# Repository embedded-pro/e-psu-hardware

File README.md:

# e-psu — Hardware

e-psu is an open-source, USB-controlled front end for a 0–30 V / 10 A bench power supply. It sets the output voltage and current limit, measures current with auto-ranging down to µA resolution, and switches the output, similar to an Otii.

This repository holds the **KiCad** design (schematic and a fully routed 4-layer PCB), the scripts that generate and route the board, and the ngspice simulation of the analog stage. The board sits between an external 30 V bench supply and the load. An STM32G474 runs the control loops' setpoints, the range switching and the USB link.

> **Scope:** this repo is the *hardware*. Firmware is not part of it. The hardware facts the firmware must respect are listed in [Firmware constraints](#firmware-constraints).

| Top | Bottom |
|---|---|
|  |  |

> **Status: rev A, not built yet.** The schematic is complete and simulated. The board is fully routed: KiCad 7 DRC shows 0 errors and 0 unconnected items. See [Before ordering](#before-ordering).

---

## Highlights

- **Tracking pre-regulator plus linear stage.** An `LM76003` buck keeps VPRE about 1.5 V above the output. An `IRFP260N` source follower then gives a clean output with low dissipation.
- **Analog CV/CC loops.** `OPA2192` voltage and current error amps are diode-ORed onto the gate drive. Setpoints come from a `DAC80502`, and the loops were compensated from ngspice stability sweeps ([report](simulation/REPORT.md)).
- **Three current ranges, switched in hardware:**
  - 3 A on a 15 mΩ shunt with `INA293`;
  - 30 mA on 1 Ω with `INA190`;
  - 300 µA on 100 Ω with `INA190`.
  
  The bypass FETs sit on an isolated gate-drive island referenced to the output. Range-up is triggered by MCU comparators through timers, without firmware latency.
- **10 A pass-through path.** A 2 mΩ shunt with `INA281`, selected by a relay, measures current at the full 300 W.
- **Output switch.** Back-to-back `NTMFS5C430N` FETs driven by a `VOM1271` photovoltaic driver. The gate is held low at reset.
- **Hardware overcurrent clamp.** STM32G474 comparators drive the TIM20 break input, so the clamp acts within about 1 µs.
- **Isolated USB-C.** `ADuM3160` isolation, `USBLC6` ESD protection, and a separate ground plane for the PC side.
- **Input protection.** TVS, reverse-polarity P-FET, and fuses on both paths.

---

## Board architecture

The schematic is an 8-sheet hierarchical design. Each sheet is one functional block:

| Sheet | Function | Key parts |
|-------|----------|-----------|
| `e-psu.kicad_sch` | Top level: block overview, power flow, ground domains | — |
| `power_input` | 30 V input protection, housekeeping rails (+5 V, +3V3, +3.3VA, +5VA, VOP) | `SMBJ33CA`, `AOD4185`, `LMR16006X`, `AMS1117`, `TLV75533` |
| `buck` | Tracking pre-regulator (VPRE = VOUT + 1.5 V by DAC injection into FB) | `LM76003` |
| `linear` | Pass element, CV/CC loops, sense buffer, setpoint DAC, OCP clamp | `IRFP260N`, `OPA2192`, `OPA192`, `INA293`, `DAC80502` |
| `ranging` | Shunt ladder, range amplifiers, isolated gate-drive island | `INA190`, `AO3400A`, `B0505S`, `CA-IS3720HS`, `UCC27524A` |
| `output` | 10 A pass-through, mode relay, back-to-back output switch, terminals | `INA281`, `HF115F`, `NTMFS5C430N`, `VOM1271` |
| `mcu` | MCU pin map, SWD, LEDs, button, board NTC | `STM32G474RET6` |
| `usb` | Isolated USB-C | `USBLC6`, `ADuM3160` |

---

## Design requirements (spec)

These are the **hard design targets** the board must meet. They are the authoritative requirements for design review and sign-off.

| # | Requirement | Target |
|---|-------------|--------|
| R1 | Input | **30 V DC** from an external bench supply. Reverse-polarity and surge protected. |
| R2 | Output voltage | **0–30 V**, programmable (CV) |
| R3 | Output current, precision path | **3 A** max, programmable current limit (CC) |
| R4 | Output current, pass-through | **10 A** (300 W) through a relay-selected low-loss path |
| R5 | Current measurement | Auto-ranging **3 A / 30 mA / 300 µA**, µA resolution, hardware range-up |
| R6 | Output control | Output switch with a **safe state at reset** (output off, gate held low) |
| R7 | Protection | Hardware overcurrent clamp, fuses, input TVS, board temperature sensor |
| R8 | Host interface | **USB-C, galvanically isolated** from the power ground |
| R9 | PCB | **4 layers**, 100 × 100 mm, JLCPCB standard process and assembly |

### As-built component capability

| Parameter | Value |
|-----------|-------|
| Pre-regulator | `LM76003` synchronous buck, 500 kHz. VPRE = 33.8 V − 31.6 × BUCK_DAC. |
| Pass element | `IRFP260N` (TO-247) source follower at the board edge, ready for a heatsink |
| Control | Analog CV/CC loops (`OPA2192`), `DAC80502` setpoints, `OPA192` sense buffer |
| Current sense | 15 mΩ + `INA293` (3 A), 1 Ω / 100 Ω + `INA190` (30 mA / 300 µA), 2 mΩ + `INA281` (10 A) |
| Range switching | `AO3400A` bypass FETs, `BAV199` clamps, isolated island (`B0505S` + `CA-IS3720HS` + `UCC27524A`) |
| Output | `HF115F` mode relay; back-to-back `NTMFS5C430N` switch with a `VOM1271` driver |
| MCU | `STM32G474RET6`: comparators and timers for OCP and range-up, SWD |
| USB | USB-C, `USBLC6-2` ESD, `ADuM3160` full-speed isolator |
| PCB | 4 layers (F sig / In1 GND / In2 power / B sig), 1.6 mm, 1 oz outer + **1 oz inner**, 244 parts |

### Simulation results

The loops were checked across corners with ngspice. The compensation changes from the sweep are in schematic rev A1:

- CV loop phase margin: worst case 35°, median 63°.
- CC loop phase margin: at least 91°.
- A dead short peaks at 33 A for 0.9 µs with the hardware OCP armed.

Details are in [`simulation/REPORT.md`](simulation/REPORT.md).

### Firmware constraints

- Clamp **BUCK_DAC ≥ 0.2 V** (VPRE = 27.5 V). At 0 V, VPRE is commanded above VIN and the buck runs at maximum duty. In reset, the DAC pin is high-impedance, which gives a safe 2 V.
- Keep the **hardware OCP armed**: COMP3/4/6 → TIM20 BRK. Without it, a short is limited only by the analog CC loop, giving tens of amps for about 95 µs.
- **Range-up is in hardware:** COMP1 → TIM1 → RANGE_B and COMP2 → TIM8 → RANGE_A. Firmware only handles range-down.
- The analog CC loop cannot limit below about 30 mA. Lower limits need firmware supervision.

---

## Repository layout

```
e-psu-hardware/
├── hardware/                       # KiCad projects — one folder per board
│   └── e-psu/                      #   main board (KiCad 7 format)
│       ├── e-psu.kicad_pro
│       ├── e-psu.kicad_sch         #     top-level (root) schematic
│       ├── power_input / buck / linear / ranging / output / mcu / usb .kicad_sch
│       ├── e-psu.kicad_pcb         #     PCB layout (4 layers)
│       ├── e-psu.kicad_sym         #     project symbols
│       ├── e-psu.pretty/           #     project footprints
│       └── sym-lib-table, fp-lib-table
├── scripts/
│   ├── export_review.py            # review package     -> review_exports/<board>/
│   ├── export_jlcpcb.py            # fab + assembly     -> manufacturing/<board>/
│   ├── export_release.py           # release bundle     -> release/<board>-<version>.zip
│   ├── visual_diff.py              # PR visual diff     -> diff/<board>/
│   ├── pcb/                        # board generator: placement, power copper, router, renders
│   └── schgen/                     # schematic generator (one-way: overwrites hardware/e-psu/)
├── simulation/                     # ngspice suite of the analog stage + REPORT.md
├── docs/
│   ├── psu-hardware-design-guide.md   # design & review knowledge base
│   └── images/                     # board renders
├── .claude/agents/psu-board-reviewer.md   # design-review agent
├── PROJECT_CONTEXT.md              # design summary, decisions, open items
└── .github/workflows/              # CI: kicad-bot, kicad-diff, pcb-quality, release
```

> Each board is a self-contained KiCad project in its own `hardware/<board>/` folder. The `.kicad_pro`, root schematic and board share that folder. Generated outputs are gitignored and go to `review_exports/<board>/`, `manufacturing/<board>/` and `release/`.

---

## Getting started

This is a [**KiCad**](https://www.kicad.org/) project saved in KiCad 7 format. It opens in KiCad 7 or newer.

1. Clone the repository:
   ```bash
   git clone https://github.com/embedded-pro/e-psu-hardware.git
   cd e-psu-hardware
   ```
2. Open `hardware/e-psu/e-psu.kicad_pro` in KiCad.
3. Use the schematic editor for the hierarchical sheets, or the PCB editor for the layout.

### Headless checks (the same ones CI runs)

With KiCad 8 or newer installed, you can run the electrical and design-rule checks locally:

```bash
kicad-cli sch erc  --output erc.json --format json hardware/e-psu/e-psu.kicad_sch
kicad-cli pcb drc  --output drc.json --format json --schematic-parity hardware/e-psu/e-psu.kicad_pcb
```

The export helpers produce the full packages:
- `python scripts/export_review.py` builds the review package;
- `python scripts/export_jlcpcb.py` builds the JLCPCB fab and assembly files.

### Regenerating the board and the simulation

- `scripts/pcb/make_board.py --own` rebuilds and re-routes the board from the schematic. It needs KiCad 7 and pcbnew; see [`scripts/pcb/README.md`](scripts/pcb/README.md).
- `simulation/sweep.py` and `simulation/make_plots.py` rerun the analog simulation with ngspice; see [`simulation/README.md`](simulation/README.md).

---

## Before ordering

1. **Replace the U201 footprint.** The `LM76003` land (TI RNP0030B, WQFN-30, 6 × 4 mm) in `e-psu.pretty` is provisional.
   - Get the real one from TI, or from LCSC/EasyEDA (C470958).
   - Save it as `e-psu:TI_RNP0030B_WQFN-30`.
   - Re-route the buck corner, either with `scripts/pcb/make_board.py --own` or by hand.
2. **Check these pinouts against the makers' drawings:**
   - K501 `HF115F`, mapped onto the KiCad Schrack RT1 footprint;
   - PS401 `B0505S`;
   - U502 `VOM1271`: pin 4 is assumed to be +.
3. **Get ERC clean.** kicad-bot runs it on every push.
4. **JLCPCB order options:**
   - 4 layers, 1.6 mm, **1 oz inner copper** (needed for the 10 A path on In2);
   - "Specify a location" for the order number (the `JLCJLCJLCJLC` text on the bottom);
   - check every rotation in the CPL preview.
5. **Add LCSC part numbers** for the passives that don't have one yet. THT parts are hand-soldered or ordered as THT assembly: banana jacks, F102, K501, Q301, PS401.

---

## Continuous integration

Every push and pull request is checked by [**kicad-bot**](https://github.com/embedded-pro/kicad-bot). It is a CI quality gate that wraps `kicad-cli`, KiBot, KiCost and KiDiff, and runs:

- **ERC / DRC verification:** electrical and design-rule checks, with schematic parity.
- **BOM availability:** distributor stock and lifecycle flags (not available in kicad-bot yet).
- **Visual diffs:** for pull requests, [`kicad-diff.yml`](.github/workflows/kicad-diff.yml) renders the base and head with `kicad-cli` and uploads red/green overlays.
- **Layout quality:** for pull requests, [`pcb-quality.yml`](.github/workflows/pcb-quality.yml) runs a hard short/clearance gate (exclusions ignored, plus the fab minimum), DRC and geometry gates (45° corners only, no mid-track branches, jogs, segments and vias per connection) with `pcb_rules.py` from the [`pcb-design-rules`](https://github.com/gabrielfrasantos/claude-hardware-skills/tree/main/plugins/hardware-design/skills/pcb-design-rules) skill. The report is in the job summary. It stays red until the board is re-laid out.

The workflow is [`.github/workflows/kicad-bot.yml`](.github/workflows/kicad-bot.yml). It uploads a `kicad-bot-output-<board>` artifact containing the report, metrics and raw violation data.

> kicad-bot is a CI guardrail, **not** a substitute for design review or sign-off. For a review, use the `psu-board-reviewer` agent in [`.claude/agents/`](.claude/agents/).

All third-party actions are **pinned to a full commit SHA**, with the version in a trailing comment, for supply-chain hardening.

## Releases

Releases are automated with [release-please](https://github.com/googleapis/release-please) and driven by [Conventional Commits](https://www.conventionalcommits.org/) (`feat:`, `fix:`, …). The flow, defined in [`.github/workflows/release.yml`](.github/workflows/release.yml):

1. Commits to `main` keep an open **release PR** with the next version bump and the `CHANGELOG.md` entries.
2. Merging that PR cuts a **GitHub Release** and a tag. The first release is `v0.1.0`.
3. On release, kicad-bot re-runs **ERC/DRC**, so a release requires a clean design. Then `scripts/export_release.py` builds `e-psu-<version>.zip` and attaches it to the release. The zip contains:
   - the schematic PDF;
   - board PDFs (copper and silkscreen, inner layers included);
   - Gerbers and drill files;
   - BOM and CPL.

Version state is tracked in [`.release-please-manifest.json`](.release-please-manifest.json). The behaviour is configured in [`release-please-config.json`](release-please-config.json).

---

## License

Released under the [CERN Open Hardware Licence Version 2 – Permissive](LICENSE) (CERN-OHL-P-2.0).

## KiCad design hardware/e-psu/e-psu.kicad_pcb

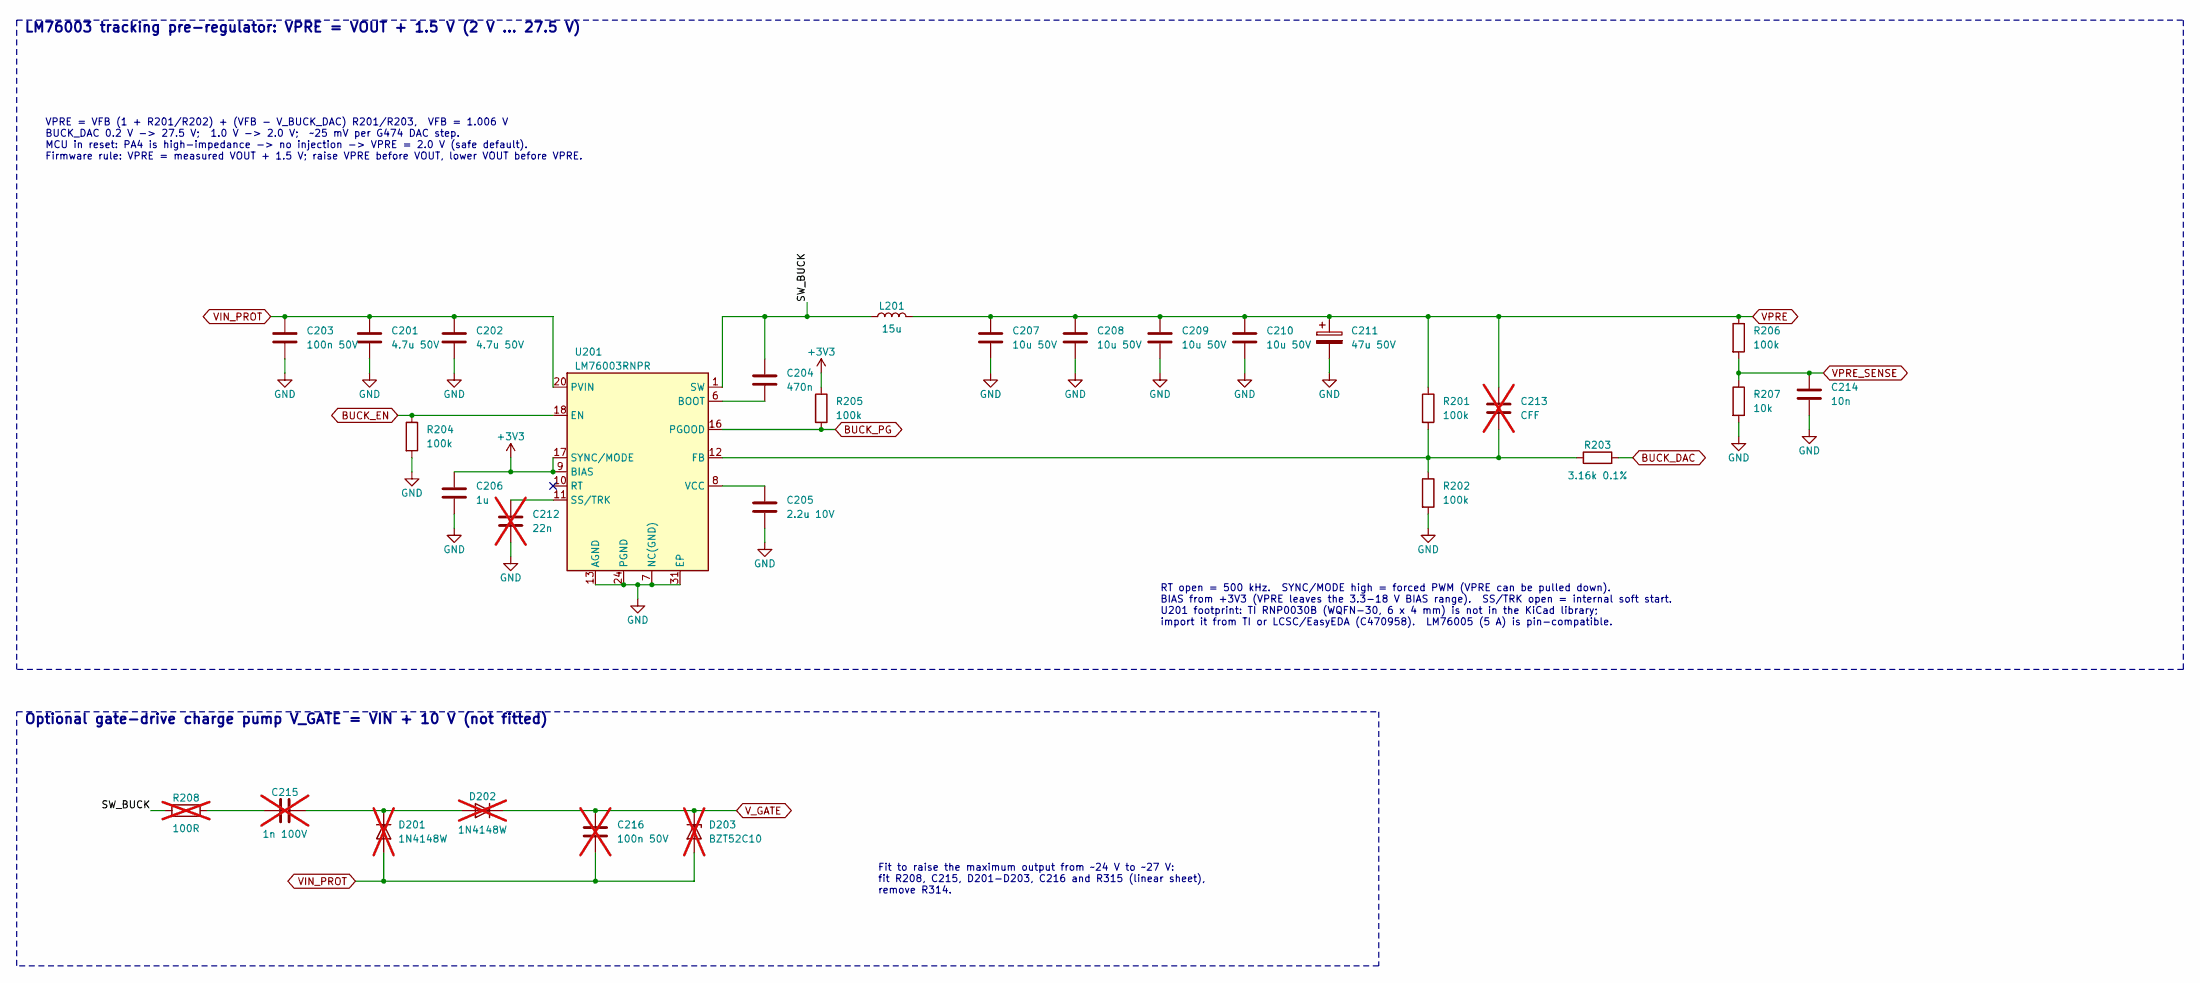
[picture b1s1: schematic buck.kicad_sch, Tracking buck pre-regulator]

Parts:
C201, C202: 4.7u 50V; C_1210_3225Metric
C203: 100n 50V; C_0603_1608Metric
C204: 470n; C_0603_1608Metric
C205: 2.2u 10V; C_0603_1608Metric
C206: 1u; C_0603_1608Metric
C207, C208, C209, C210: 10u 50V; C_1210_3225Metric
C211: 47u 50V; CP_Elec_8x10
C212: 22n; C_0603_1608Metric; not fitted
C213: CFF; C_0603_1608Metric; not fitted
C214: 10n; C_0603_1608Metric
C215: 1n 100V; C_0603_1608Metric; not fitted
C216: 100n 50V; C_0603_1608Metric; not fitted
D201, D202: 1N4148W; D_SOD-123; not fitted
D203: BZT52C10; D_SOD-123; not fitted
L201: 15u; L_Wuerth_HCI-1350; MPN FANGCHENG FCH1365-150M (Isat 12 A); LCSC C20415554
R201, R202, R204, R205, R206: 100k; R_0603_1608Metric
R203: 3.16k 0.1%; R_0603_1608Metric
R207: 10k; R_0603_1608Metric
R208: 100R; R_0603_1608Metric; not fitted
U201: LM76003RNPR; TI_RNP0030B_WQFN-30; MPN TI LM76003RNPR; LCSC C470958

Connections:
+3V3: C206.1, R205.1, U201.9 (BIAS), U201.17 (SYNC/MODE); also elsewhere on the board
/Tracking buck pre-regulator/SW_BUCK: C204.1, L201.1, R208.1, U201.1 (SW), U201.2 (SW), U201.3 (SW), U201.4 (SW), U201.5 (SW)
BUCK_DAC: R203.2; also elsewhere on the board
BUCK_EN: R204.1, U201.18 (EN); also elsewhere on the board
BUCK_PG: R205.2, U201.16 (PGOOD); also elsewhere on the board
GND: C201.2, C202.2, C203.2, C205.2, C206.2, C207.2, C208.2, C209.2, C210.2, C211.2, C212.2, C214.2, R202.2, R204.2, R207.2, U201.7 (NC(GND)), U201.13 (AGND), U201.14 (AGND), U201.15 (AGND), U201.19 (NC(GND)), U201.23 (NC(GND)), U201.24 (PGND), U201.25 (PGND), U201.26 (PGND), U201.27 (NC(GND)), U201.28 (NC(GND)), U201.29 (NC(GND)), U201.30 (NC(GND)), U201.31 (EP); also elsewhere on the board
unnamed: C215.1, R208.2
unnamed: C215.2, D201.1 (K), D202.2 (A)
unnamed: C204.2, U201.6 (BOOT)
unnamed: C213.2, R201.2, R202.1, R203.1, U201.12 (FB)
unnamed: C212.1, U201.11 (SS/TRK)
unnamed: C205.1, U201.8 (VCC)
VIN_PROT: C201.1, C202.1, C203.1, C216.2, D201.2 (A), D203.2 (A), U201.20 (PVIN), U201.21 (PVIN), U201.22 (PVIN); also elsewhere on the board
VPRE: C207.1, C208.1, C209.1, C210.1, C211.1, C213.1, L201.2, R201.1, R206.1; also elsewhere on the board
VPRE_SENSE: C214.1, R206.2, R207.1; also elsewhere on the board
V_GATE: C216.1, D202.1 (K), D203.1 (K); also elsewhere on the board

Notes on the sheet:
LM76003 tracking pre-regulator: VPRE = VOUT + 1.5 V (2 V ... 27.5 V)
VPRE = VFB (1 + R201/R202) + (VFB - V_BUCK_DAC) R201/R203, VFB = 1.006 V BUCK_DAC 0.2 V -> 27.5 V; 1.0 V -> 2.0 V; ~25 mV per G474 DAC step. MCU in reset: PA4 is high-impedance -> no injection -> VPRE = 2.0 V (safe default). Firmware rule: VPRE = measured VOUT + 1.5 V; raise VPRE before VOUT, lower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
RT open = 500 kHz. SYNC/MODE high = forced PWM (VPRE can be pulled down). BIAS from +3V3 (VPRE leaves the 3.3-18 V BIAS range). SS/TRK open = internal soft start. U201 footprint: TI RNP0030B (WQFN-30, 6 x 4 mm) is not in the KiCad library; import it from TI or LCSC/EasyEDA (C470958). LM76005 (5 A) 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
Optional gate-drive charge pump V_GATE = VIN + 10 V (not fitted)
Fit to raise the maximum output from ~24 V to ~27 V: fit R208, C215, D201-D203, C216 and R315 (linear sheet), remove R314.

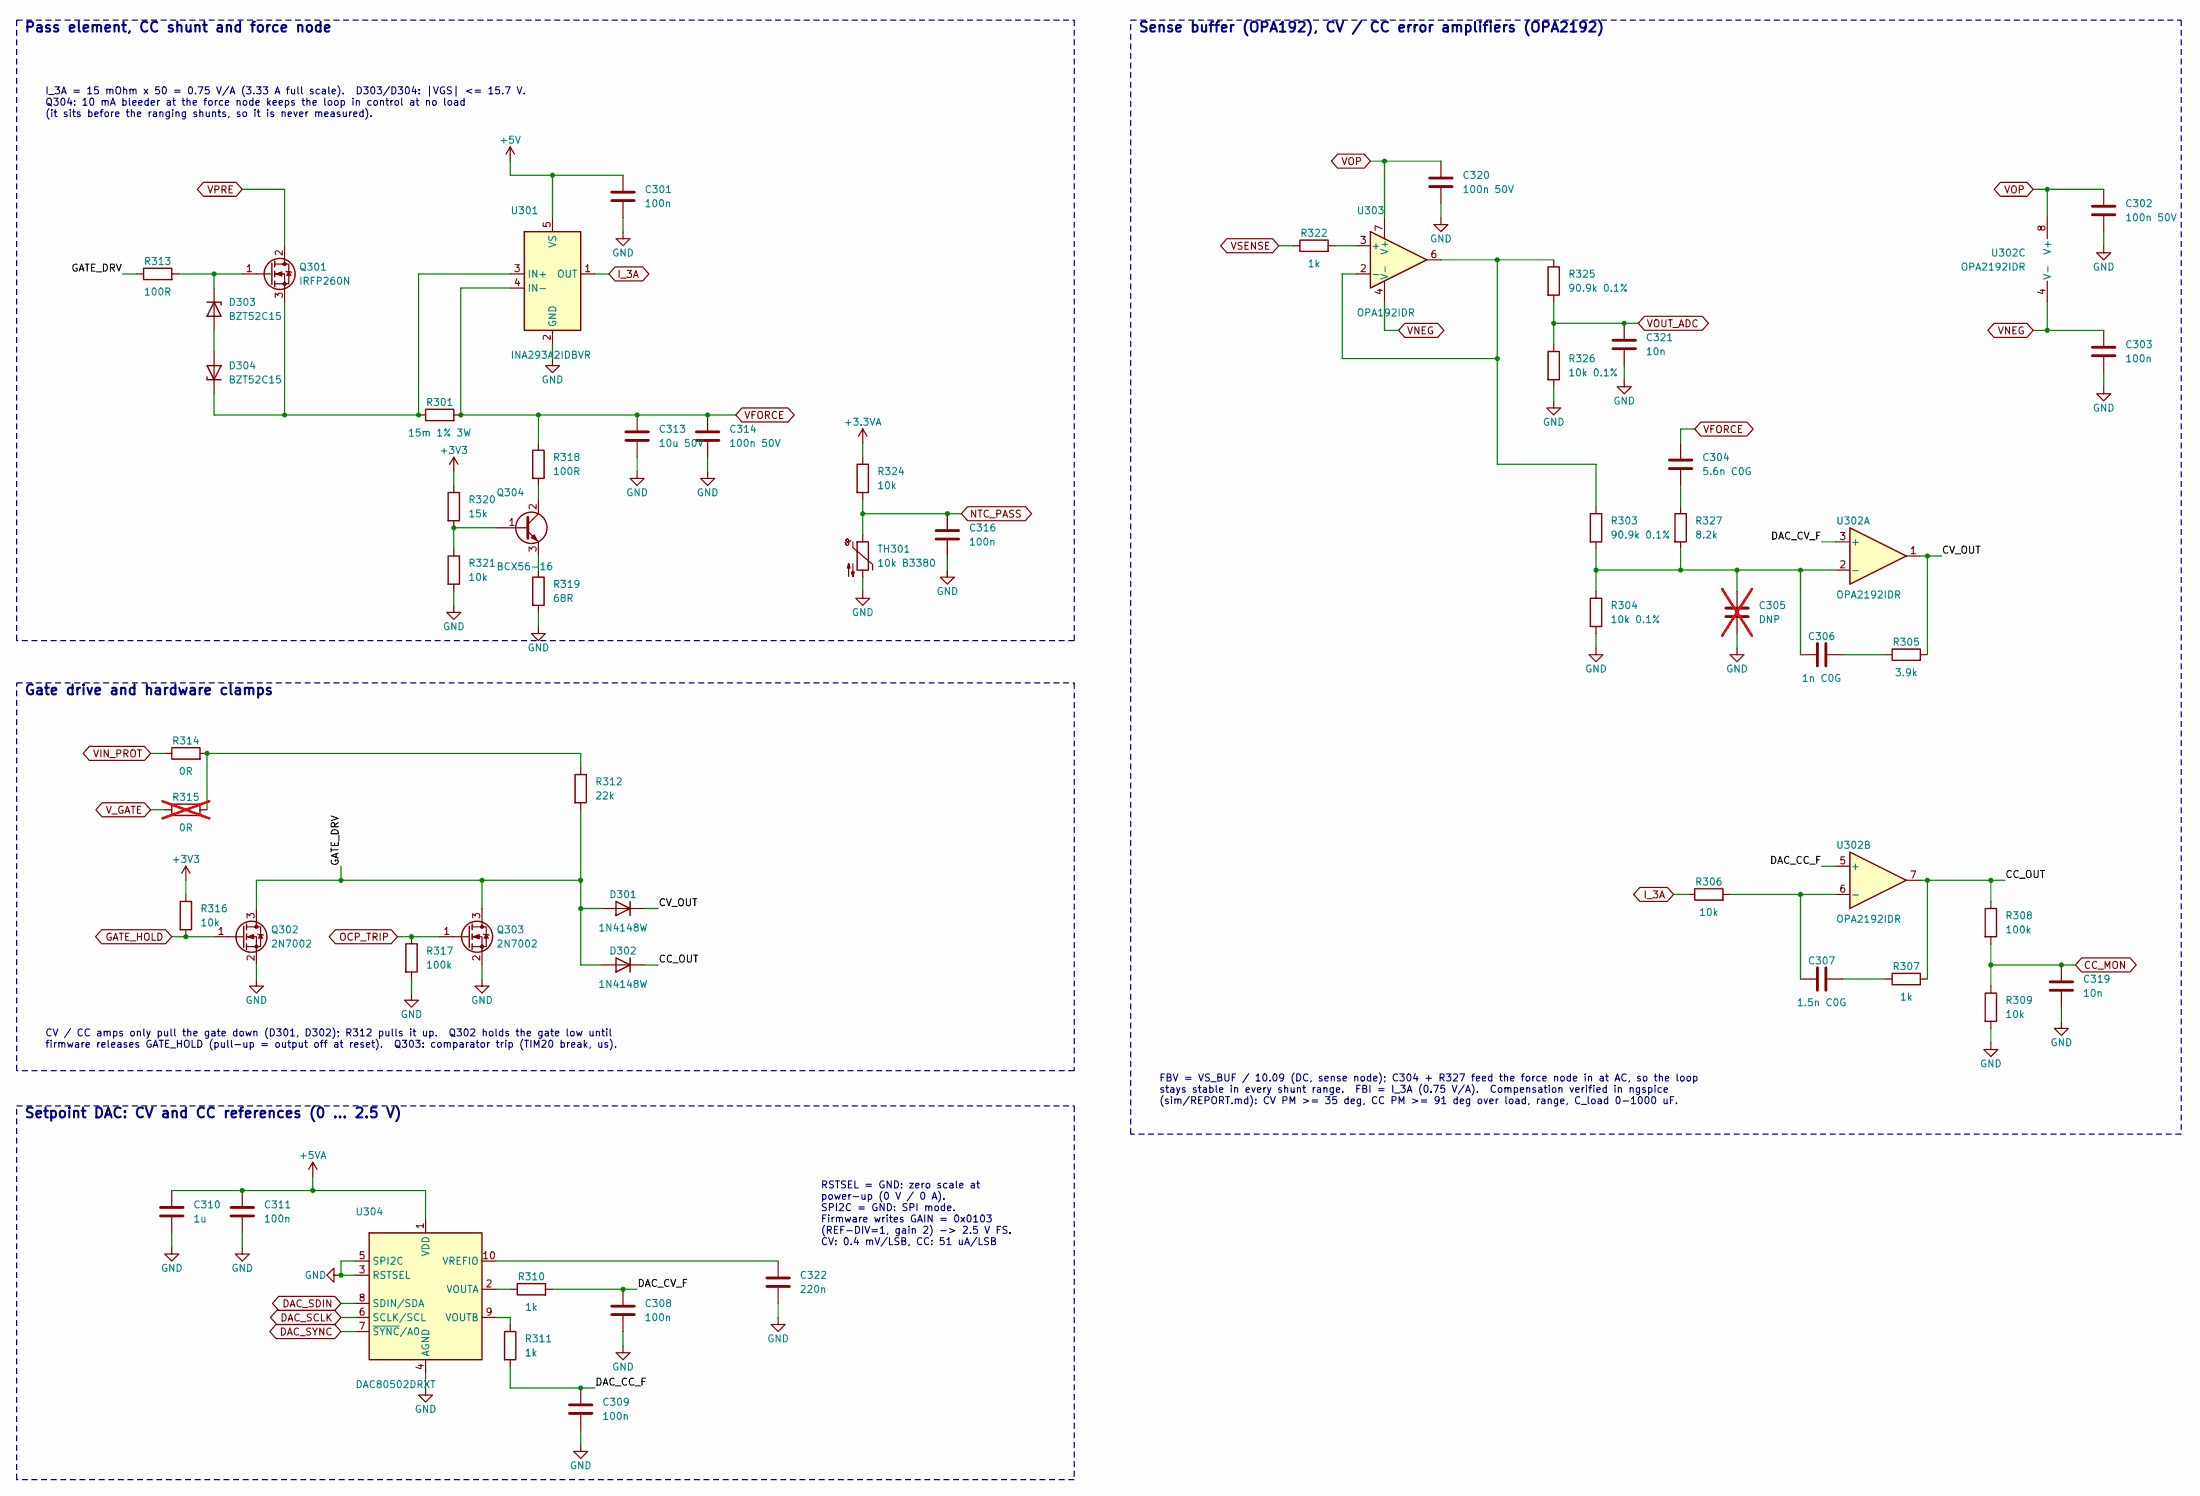
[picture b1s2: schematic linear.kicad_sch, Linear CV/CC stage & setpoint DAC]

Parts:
C301, C303, C308, C309, C311, C316: 100n; C_0603_1608Metric
C302, C314, C320: 100n 50V; C_0603_1608Metric
C304: 5.6n C0G; C_0603_1608Metric
C305: DNP; C_0603_1608Metric; not fitted
C306: 1n C0G; C_0603_1608Metric
C307: 1.5n C0G; C_0603_1608Metric
C310: 1u; C_0603_1608Metric
C313: 10u 50V; C_1210_3225Metric
C319, C321: 10n; C_0603_1608Metric
C322: 220n; C_0603_1608Metric
D301, D302: 1N4148W; D_SOD-123
D303, D304: BZT52C15; D_SOD-123
Q301: IRFP260N; TO-247-3_Vertical; MPN Infineon IRFP260NPBF on heatsink (or a 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; LCSC C2678
Q302, Q303: 2N7002; SOT-23
Q304: BCX56-16; SOT-89-3; MPN BCX56-16 (SOT-89, 1 W): ~0.25 W at 24 V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
R301: 15m 1% 3W; R_2512_6332Metric; LCSC C459682
R303, R325: 90.9k 0.1%; R_0603_1608Metric
R304, R326: 10k 0.1%; R_0603_1608Metric
R305: 3.9k; R_0603_1608Metric
R306, R309, R316, R321, R324: 10k; R_0603_1608Metric
R307, R310, R311, R322: 1k; R_0603_1608Metric
R308, R317: 100k; R_0603_1608Metric
R312: 22k; R_0603_1608Metric
R313, R318: 100R; R_0603_1608Metric
R314: 0R; R_0603_1608Metric
R315: 0R; R_0603_1608Metric; not fitted
R319: 68R; R_0805_2012Metric
R320: 15k; R_0603_1608Metric
R327: 8.2k; R_0603_1608Metric
TH301: 10k B3380; R_0603_1608Metric; MPN Murata NCP18XH103F03RB, on the heatsink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; LCSC C13564
U301: INA293A2IDBVR; SOT-23-5; LCSC C1855792
U302: OPA2192IDR; SOIC-8_3.9x4.9mm_P1.27mm; LCSC C110074
U303: OPA192IDR; SOIC-8_3.9x4.9mm_P1.27mm; LCSC C2861286
U304: DAC80502DRXT; Texas_DRX_WSON-10_2.5x2.5mm_P0.5mm; LCSC C2861168

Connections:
+3.3VA: R324.1; also elsewhere on the board
+3V3: R316.1, R320.1; also elsewhere on the board
+5V: C301.1, U301.5 (VS); also elsewhere on the board
+5VA: C310.1, C311.1, U304.1 (VDD); also elsewhere on the board
/Linear CV/CC stage & setpoint DAC/CC_OUT: D302.1 (K), R307.2, R308.1, U302.7
/Linear CV/CC stage & setpoint DAC/CV_OUT: D301.1 (K), R305.2, U302.1
/Linear CV/CC stage & setpoint DAC/DAC_CC_F: C309.1, R311.2, U302.5 (+)
/Linear CV/CC stage & setpoint DAC/DAC_CV_F: C308.1, R310.2, U302.3 (+)
/Linear CV/CC stage & setpoint DAC/GATE_DRV: D301.2 (A), D302.2 (A), Q302.3 (D), Q303.3 (D), R312.2, R313.1
CC_MON: C319.1, R308.2, R309.1; also elsewhere on the board
DAC_SCLK: U304.6 (SCLK/SCL); also elsewhere on the board
DAC_SDIN: U304.8 (SDIN/SDA); also elsewhere on the board
DAC_SYNC: U304.7 (~SYNC/A0); also elsewhere on the board
GATE_HOLD: Q302.1 (G), R316.2; also elsewhere on the board
GND: C301.2, C302.2, C303.2, C305.2, C308.2, C309.2, C310.2, C311.2, C313.2, C314.2, C316.2, C319.2, C320.2, C321.2, C322.2, Q302.2 (S), Q303.2 (S), R304.2, R309.2, R317.2, R319.2, R321.2, R326.2, TH301.2, U301.2 (GND), U304.3 (RSTSEL), U304.4 (AGND), U304.5 (SPI2C); also elsewhere on the board
I_3A: R306.1, U301.1 (OUT); also elsewhere on the board
NTC_PASS: C316.1, R324.2, TH301.1; also elsewhere on the board
unnamed: C304.2, R327.1
unnamed: C306.2, R305.1
unnamed: C307.2, R307.1
unnamed: D303.2 (A), D304.2 (A)
unnamed: D303.1 (K), Q301.1 (G), R313.2
unnamed: D304.1 (K), Q301.3 (S), R301.1, U301.3 (IN+)
unnamed: Q304.1 (B), R320.2, R321.1
unnamed: Q304.2 (C), R318.2
unnamed: Q304.3 (E), R319.1
unnamed: R312.1, R314.2, R315.2
unnamed: C305.1, C306.1, R303.2, R304.1, R327.2, U302.2 (-)
unnamed: C307.1, R306.2, U302.6 (-)
unnamed: R322.2, U303.3 (+)
unnamed: R303.1, R325.1, U303.2 (-), U303.6
unnamed: R310.1, U304.2 (VOUTA)
unnamed: R311.1, U304.9 (VOUTB)
unnamed: C322.1, U304.10 (VREFIO)
OCP_TRIP: Q303.1 (G), R317.1; also elsewhere on the board
VFORCE: C304.1, C313.1, C314.1, R301.2, R318.1, U301.4 (IN-); also elsewhere on the board
VIN_PROT: R314.1; also elsewhere on the board
VNEG: C303.1, U302.4 (V-), U303.4 (V-); also elsewhere on the board
VOP: C302.1, C320.1, U302.8 (V+), U303.7 (V+); also elsewhere on the board
VOUT_ADC: C321.1, R325.2, R326.1; also elsewhere on the board
VPRE: Q301.2 (D); also elsewhere on the board
VSENSE: R322.1; also elsewhere on the board
V_GATE: R315.1; also elsewhere on the board

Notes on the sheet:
Pass element, CC shunt and force node
I_3A = 15 mOhm x 50 = 0.75 V/A (3.33 A full scale). D303/D304: |VGS| <= 15.7 V. Q304: 10 mA bleeder at the force node keeps the loop in control at no load (it sits before the ranging shunts, so it is never measured).
Gate drive and hardware clamps
CV / CC amps only pull the gate down (D301, D302); R312 pulls it up. Q302 holds the gate low until firmware releases GATE_HOLD (pull-up = output off at reset). Q303: comparator trip (TIM20 break, us).
Setpoint DAC: CV and CC references (0 ... 2.5 V)
RSTSEL = GND: zero scale at power-up (0 V / 0 A). SPI2C = GND: SPI mode. Firmware writes GAIN = 0x0103 (REF-DIV=1, gain 2) -> 2.5 V FS. CV: 0.4 mV/LSB, CC: 51 uA/LSB
Sense buffer (OPA192), CV / CC error amplifiers (OPA2192)
FBV = VS_BUF / 10.09 (DC, sense node); C304 + R327 feed the force node in at AC, so the loop stays stable in every shunt range. FBI = I_3A (0.75 V/A). Compensation verified in ngspice (sim/REPORT.md): CV PM >= 35 deg, CC PM >= 91 deg over load, range, C_load 0-1000 uF.

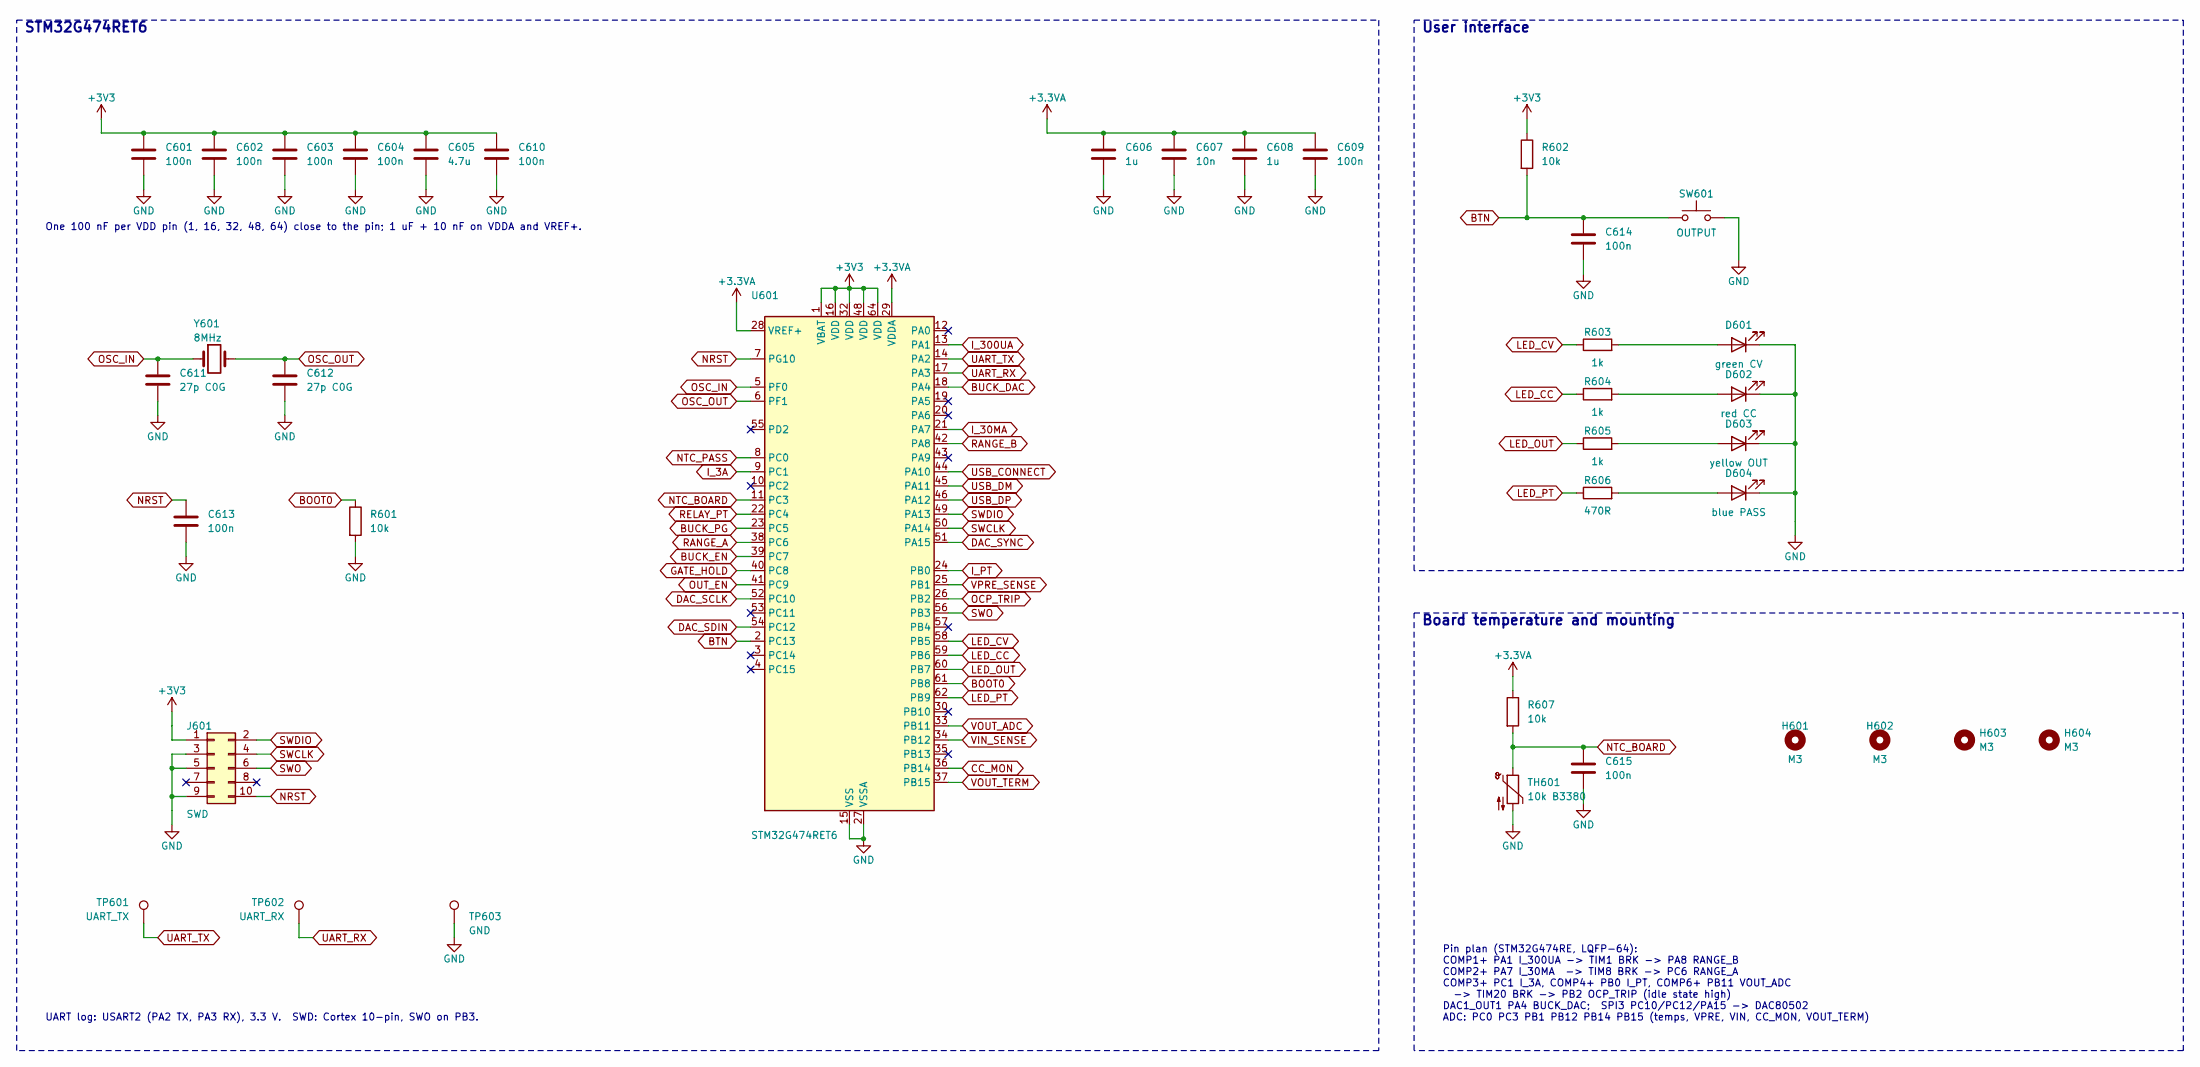
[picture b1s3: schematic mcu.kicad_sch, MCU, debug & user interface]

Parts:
C601, C602, C603, C604, C609, C610, C613, C614, C615: 100n; C_0603_1608Metric
C605: 4.7u; C_0805_2012Metric
C606, C608: 1u; C_0603_1608Metric
C607: 10n; C_0603_1608Metric
C611, C612: 27p C0G; C_0603_1608Metric
D601: green CV; LED_0603_1608Metric
D602: red CC; LED_0603_1608Metric
D603: yellow OUT; LED_0603_1608Metric
D604: blue PASS; LED_0603_1608Metric
H601, H602, H603, H604: M3; MountingHole_3.2mm_M3
J601: SWD; PinHeader_2x05_P1.27mm_Vertical_SMD; MPN Cortex debug 2x5 1.27 mm; LCSC C5160761
R601, R602, R607: 10k; R_0603_1608Metric
R603, R604, R605: 1k; R_0603_1608Metric
R606: 470R; R_0603_1608Metric
SW601: OUTPUT; SW_SPST_PTS645
TH601: 10k B3380; R_0603_1608Metric; LCSC C13564
TP601: UART_TX; TestPoint_Pad_D1.5mm
TP602: UART_RX; TestPoint_Pad_D1.5mm
TP603: GND; TestPoint_Pad_D1.5mm
U601: STM32G474RET6; LQFP-64_10x10mm_P0.5mm; MPN STM32G474RET6 (fallback STM32G431RBT6, 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; LCSC C521608
Y601: 8MHz; Crystal_SMD_HC49-SD; LCSC C12674

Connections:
+3.3VA: C606.1, C607.1, C608.1, C609.1, R607.1, U601.28 (VREF+), U601.29 (VDDA); also elsewhere on the board
+3V3: C601.1, C602.1, C603.1, C604.1, C605.1, C610.1, J601.1, R602.1, U601.1 (VBAT), U601.16 (VDD), U601.32 (VDD), U601.48 (VDD), U601.64 (VDD); also elsewhere on the board
BOOT0: R601.1, U601.61 (PB8)
BTN: C614.1, R602.2, SW601.1, U601.2 (PC13)
BUCK_DAC: U601.18 (PA4); also elsewhere on the board
BUCK_EN: U601.39 (PC7); also elsewhere on the board
BUCK_PG: U601.23 (PC5); also elsewhere on the board
CC_MON: U601.36 (PB14); also elsewhere on the board
DAC_SCLK: U601.52 (PC10); also elsewhere on the board
DAC_SDIN: U601.54 (PC12); also elsewhere on the board
DAC_SYNC: U601.51 (PA15); also elsewhere on the board
GATE_HOLD: U601.40 (PC8); also elsewhere on the board
GND: C601.2, C602.2, C603.2, C604.2, C605.2, C606.2, C607.2, C608.2, C609.2, C610.2, C611.2, C612.2, C613.2, C614.2, C615.2, D601.1 (K), D602.1 (K), D603.1 (K), D604.1 (K), J601.3, J601.5, J601.9, R601.2, SW601.2, TH601.2, TP603.1, U601.15 (VSS), U601.27 (VSSA), U601.31 (VSS), U601.47 (VSS), U601.63 (VSS); also elsewhere on the board
I_3A: U601.9 (PC1); also elsewhere on the board
I_30MA: U601.21 (PA7); also elsewhere on the board
I_300UA: U601.13 (PA1); also elsewhere on the board
I_PT: U601.24 (PB0); also elsewhere on the board
LED_CC: R604.1, U601.59 (PB6)
LED_CV: R603.1, U601.58 (PB5)
LED_OUT: R605.1, U601.60 (PB7)
LED_PT: R606.1, U601.62 (PB9)
NRST: C613.1, J601.10, U601.7 (PG10)
NTC_BOARD: C615.1, R607.2, TH601.1, U601.11 (PC3)
NTC_PASS: U601.8 (PC0); also elsewhere on the board
unnamed: D601.2 (A), R603.2
unnamed: D602.2 (A), R604.2
unnamed: D603.2 (A), R605.2
unnamed: D604.2 (A), R606.2
OCP_TRIP: U601.26 (PB2); also elsewhere on the board
OSC_IN: C611.1, U601.5 (PF0), Y601.1
OSC_OUT: C612.1, U601.6 (PF1), Y601.2
OUT_EN: U601.41 (PC9); also elsewhere on the board
RANGE_A: U601.38 (PC6); also elsewhere on the board
RANGE_B: U601.42 (PA8); also elsewhere on the board
RELAY_PT: U601.22 (PC4); also elsewhere on the board
SWCLK: J601.4, U601.50 (PA14)
SWDIO: J601.2, U601.49 (PA13)
SWO: J601.6, U601.56 (PB3)
UART_RX: TP602.1, U601.17 (PA3)
UART_TX: TP601.1, U601.14 (PA2)
USB_CONNECT: U601.44 (PA10); also elsewhere on the board
USB_DM: U601.45 (PA11); also elsewhere on the board
USB_DP: U601.46 (PA12); also elsewhere on the board
VIN_SENSE: U601.34 (PB12); also elsewhere on the board
VOUT_ADC: U601.33 (PB11); also elsewhere on the board
VOUT_TERM: U601.37 (PB15); also elsewhere on the board
VPRE_SENSE: U601.25 (PB1); also elsewhere on the board

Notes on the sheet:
STM32G474RET6
One 100 nF per VDD pin (1, 16, 32, 48, 64) close to the pin; 1 uF + 10 nF on VDDA and VREF+.
UART log: USART2 (PA2 TX, PA3 RX), 3.3 V. SWD: Cortex 10-pin, SWO on PB3.
User interface
Board temperature and mounting
Pin plan (STM32G474RE, LQFP-64): COMP1+ PA1 I_300UA -> TIM1 BRK -> PA8 RANGE_B COMP2+ PA7 I_30MA -> TIM8 BRK -> PC6 RANGE_A COMP3+ PC1 I_3A, COMP4+ PB0 I_PT, COMP6+ PB11 VOUT_ADC -> TIM20 BRK -> PB2 OCP_TRIP (idle state high) DAC1_OUT1 PA4 BUCK_DAC; SPI3 PC10/PC12/PA15 -> DAC80502 ADC: PC0 PC3 PB1 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
